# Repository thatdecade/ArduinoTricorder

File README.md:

# ArduinoTricorder
Interactive Tricorder Prop with real environmental sensors

Based on the original work by lambtor: https://github.com/lambtor/ArduinoTricorder

# Features

* Animated Lights and Sounds, Interactive Menus
* Thermal Camera (MLX90640)
* Climate Sensors: Humidity (SHT31), Temperature and barometric pressure (BMP280)
* Color Sensor and Distance Measurement (APDS9960)
* Microphone (PDM) FFT spectrum
* Auto Sleep when Door is Closed, uses Magnetometer (LIS3MDL)

# Usage

On Power up, the main screen is displayed and the sound effects start.  

* To navigate the info pages, press left or right.  Pressing center goes home.
* To toggle sound effects, hold the left button.
* Close the lid or wait 10 mins to put to sleep, low power mode.  Open the lid or press a button to wake up.

Thermal Camera: To access the video, press the button marked User SW on the Feather board.  If you did not install the thermal camera, the tricorder will display an error message.
Press the center button to return home.

# Part List

TBD

# 3D Printing

The case assembly notes are on printables: https://www.printables.com/model/225964-printability-remix-of-arduino-tricorder

# Wiring Diagram

Battery, Charger Jack, and Power Switch not shown.  See Adafruit Feather nRF52840 Sense docs.

I used a 2500mAh battery, but smaller would work fine too.  1000mAh - 2500mAh is recommended.

If you want to change any wires, use the pinmap.h file.  

# Software Setup

Follow the adafruit guide for setting up the Feather nRF52840 board package in Arduino. Then begin installing the libraries.
https://learn.adafruit.com/adafruit-feather-sense/arduino-support-setup

1. Copy the MLX90640_API folder from this repo's libraries folder to your arduino's libraries folder.  If you are unsure where this is, open Preferences from the Arduino File menu and look for the sktechbook location. Mine is My Documents\Arduino\libraries.
1. Install the following lilbraries.  Start with the latest versions.
> * Adafruit NeoPixel version 1.10.6
> * Adafruit TinyUSB Library version 1.7.0
> * Adafruit GFX Library version 1.11.3
> * Adafruit BusIO version 1.14.1
> * Adafruit ST7735 and ST7789 Library 
> * Adafruit APDS9960 Library version 1.2.2
> * Adafruit BMP280 Library version 2.6.6
> * Adafruit Unified Sensor version 1.1.6
> * Adafruit SHT31 Library version 2.2.0
> * nRF52840 PDM - Adafruit Fork version 1.0
> * Adafruit Zero FFT Library version 1.0.4
> * Adafruit LIS3MDL version 1.2.1
> * DFRobotDFPlayerMini version 1.0.5
3. Hit the Compile to test everything is as it should be.  If you get any errors, try switching to the version listed above.
4. Plug in the arduino to USB, and select Adafruit Feather nRF52840 Sense as the board, then select the port.
5. Hit Upload.

If all went well, you should see the display come alive.

# Bugs

* I used D13 for the BIO button input and needed to remove the Arduino's D13 onboard LED.  

On the Adafruit Feather nRF52840 Sense board, D13 is wired to an onboard LED (similar to other arduino boards).  D13 worked at first using INPUT_PULLUP, but eventually stopped working.  I measured the voltage on this pin at 1.9V when the button was unpressed, and 0.2V for pressed.  The nRF52840 requires at least 0.7xVcc to detect a digital high.  1.9V < 2.3V, so the chip thought the button was stuck pressed.  The LED + Resistor and INPUT_PULLUP were creating a voltage clamp at the diode's Forward Voltage.

My fix was unsoldering the D13 LED.  A better fix would be moving the BIO button input wire and reserving D13 as output only.

* Communication with the DFPlayer is inconsistant.

Likely due to me using a clone of the DFPlayer.  Work around is for the arduino to query the status from the DFPlayer every 500ms, then if the player is not playing when it should (or vice versa) we send the play/stop command again.  So if there is a glitch in the audio start / loop / stop, it is fixed quickly.

* Speaker Volume and Screen Flicker, reduce volume and use a larger battery

When the DFPlayer is set to max volume and the tricorder is powered by USB, I noticed the screen flickering from the speaker amp.  Switching to battery, the screen appears ok.

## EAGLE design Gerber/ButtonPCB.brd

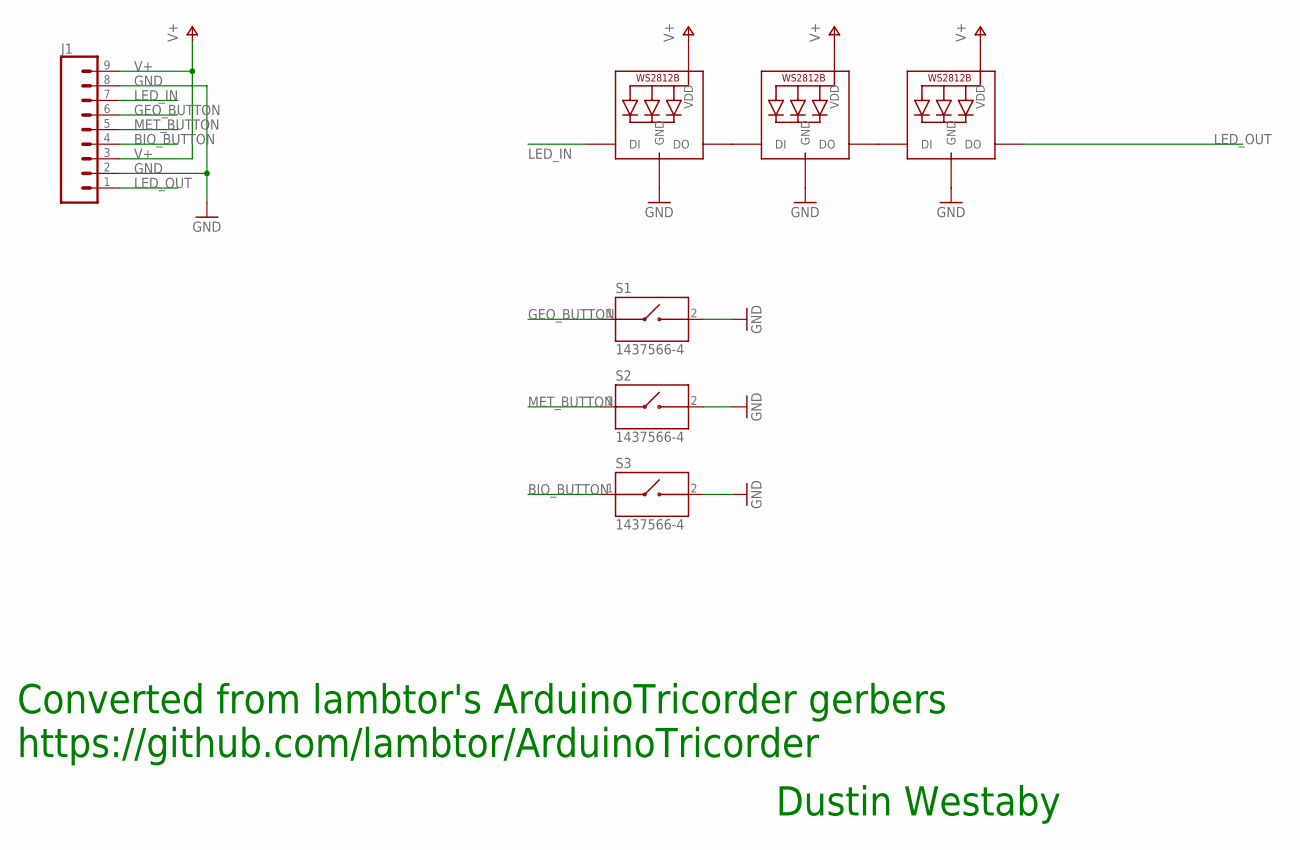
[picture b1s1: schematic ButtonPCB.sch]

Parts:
J1: CONN_09; 1X09
LED1, LED2, LED3: WS2812B_4020
S1, S2, S3: 1437566-4; SW_1437566-4

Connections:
BIO_BUTTON: J1.4, S3.1
GEO_BUTTON: J1.6, S1.1
GND: J1.2, J1.8, LED1.4 (GND), LED2.4 (GND), LED3.4 (GND), S1.2, S2.2, S3.2
LED_IN: J1.7, LED2.1 (DI)
LED_OUT: J1.1, LED3.3 (DO)
MET_BUTTON: J1.5, S2.1
unnamed: LED1.1 (DI), LED2.3 (DO)
unnamed: LED1.3 (DO), LED3.1 (DI)
V+: J1.3, J1.9, LED1.2 (VDD), LED2.2 (VDD), LED3.2 (VDD)

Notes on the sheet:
Converted from lambtor's ArduinoTricorder gerbers
https://github.com/lambtor/ArduinoTricorder
Dustin Westaby

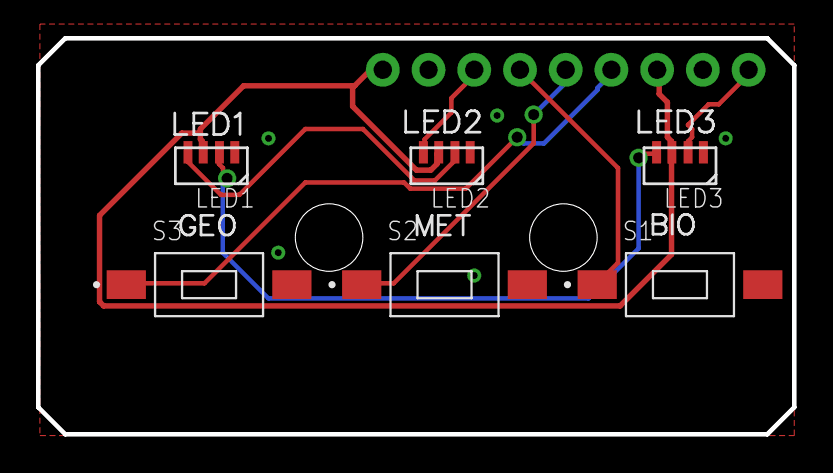
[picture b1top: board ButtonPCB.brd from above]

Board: 2 copper layers, 42.0 x 22.0 mm, 7 parts (1 on the bottom side), 9 nets.

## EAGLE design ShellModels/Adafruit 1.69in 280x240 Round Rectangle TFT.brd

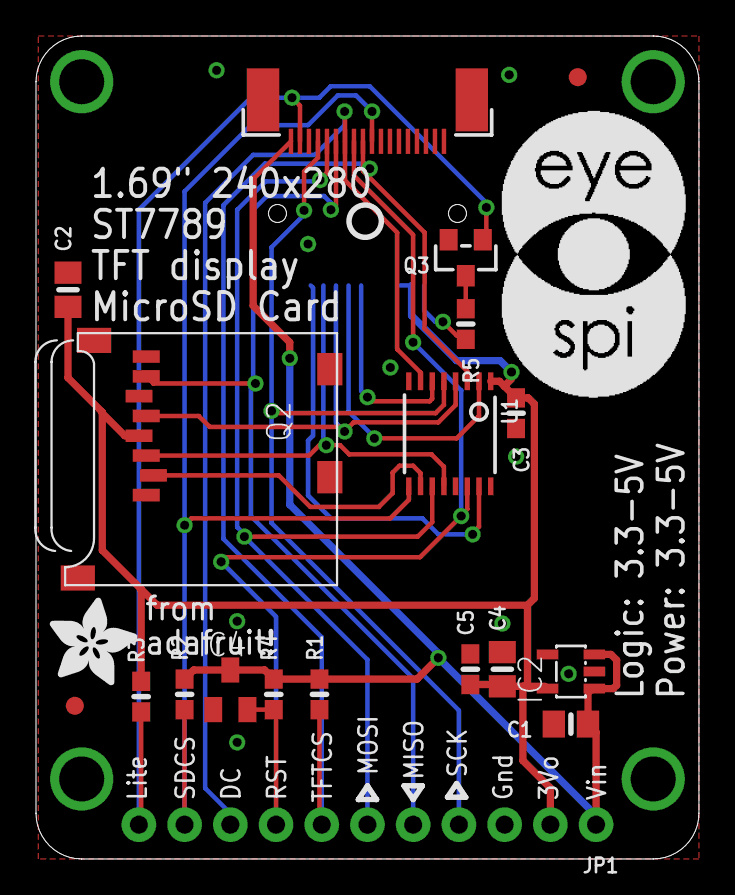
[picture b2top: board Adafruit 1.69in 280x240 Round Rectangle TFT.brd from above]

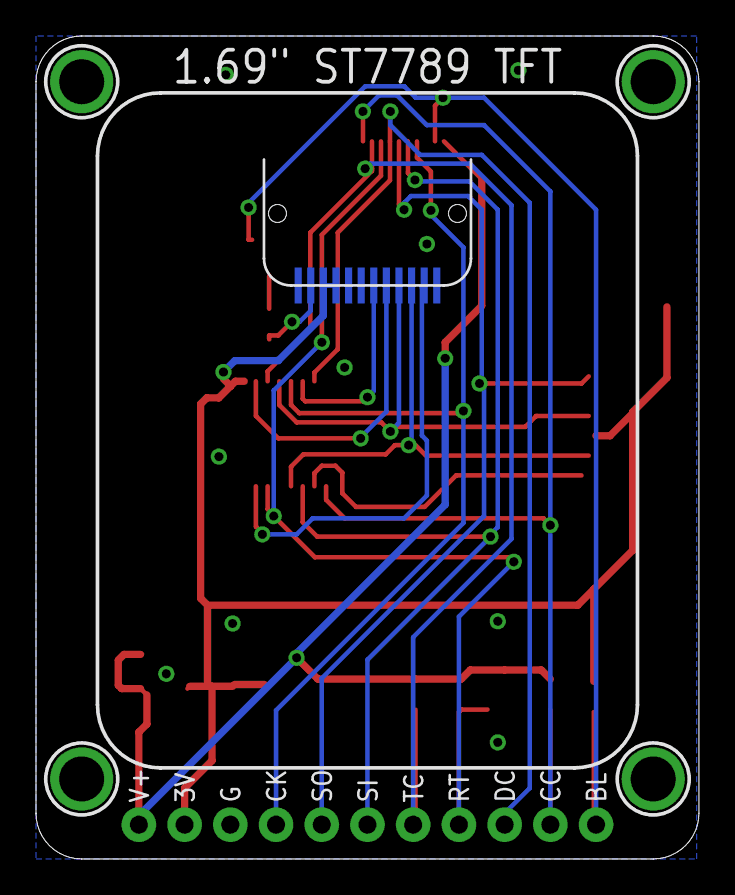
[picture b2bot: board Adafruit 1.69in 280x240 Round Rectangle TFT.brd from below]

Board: 2 copper layers, 36.8 x 45.7 mm, 27 parts (5 on the bottom side), 19 nets.

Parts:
C1, C2, C4: 10uF; 0805-NO
C3, C5: 0.1uF; 0603-NO
DISP1: DISP_LCD_GENERIC_SPI_1.69_WRAPUNDER; TFT_1.69IN_240X280_12P
IC2: AP2112; SOT23-5L
IC4: APX803-SAG; SOT23
JP1: 1X11_ROUND_76
Q2: MICROSD
Q3: BSS138; SOT23-WIDE
R1, R2, R3, R4: 10K; 0603-NO
R5: 10; 0603-NO
U1: 74HC4050PWR; TSSOP16
U$1: ADAFRUIT_5MM
U$2: PCBFEAT-REV-040
U$4, U$5: FIDUCIAL_1MM
U$7, U$8, U$9, U$10: MOUNTINGHOLE2.5; MOUNTINGHOLE_2.5_PLATED
U$19: EYESPI_LOGO
X1: EYE_SPI_DISPLAY_FLIP; EYE_SPI_DISPLAY_BOTCONTACT

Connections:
+3V3: C2.1, C3.1, C4.1, C5.1, DISP1.3, DISP1.4, IC2.5, JP1.2, Q2.4, R3.2, U1.1
CARDCS: JP1.10, R2.1, U1.9, X1.10
CARDCS_3V: Q2.2, U1.10
GND: C1.2, C2.2, C3.2, C4.2, C5.2, DISP1.1, DISP1.5, DISP1.6, DISP1.12, IC2.2, IC4.1, JP1.3, Q2.6, Q2.MT1, Q2.MT2, Q3.2, U1.8, X1.3, X1.SUPPORT1, X1.SUPPORT2
LEDK: DISP1.2, R5.2
LITE: JP1.11, Q3.1, R3.1, X1.2
MISO: JP1.5, Q2.7, X1.6
MOSI: JP1.6, U1.11, X1.5
MOSI_3V: DISP1.10, Q2.3, U1.12
unnamed: Q3.3, R5.1
SCK: JP1.4, U1.5, X1.4
SCK_3V: DISP1.9, Q2.5, U1.4
TFTCS: JP1.7, R1.1, U1.3, X1.9
TFTCS_3V: DISP1.8, U1.2
TFTDC: JP1.9, U1.7, X1.7
TFTDC_3V: DISP1.7, U1.6
TFTRST: IC4.2, JP1.8, R4.1, U1.14, X1.8
TFTRST_3V: DISP1.11, U1.15
VIN: C1.1, IC2.1, IC2.3, IC4.3, JP1.1, R1.2, R2.2, R4.2, X1.1

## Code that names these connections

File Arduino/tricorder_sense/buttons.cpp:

/*
 * buttons.c
 *
 *  Created on: Jul 15, 2020
 *      Author: Dustin Westaby
 */

#include "buttons.h"
#include "pinmap.h" // go here to set your own pin definitions

byte pinMap_buttons[NUMBER_OF_BUTTONS] =
{
  GEO_BUTTON_1_PIN,  // GEO_BUTTON
  MET_BUTTON_2_PIN,  // MET_BUTTON
  BIO_BUTTON_3_PIN,  // BIO_BUTTON
  CAM_BUTTON_BOARD,  // CAM_BUTTON
};

byte button_state[NUMBER_OF_BUTTONS] = 
{
  IS_NOT_PRESSED,  // GEO_BUTTON
  IS_NOT_PRESSED,  // MET_BUTTON
  IS_NOT_PRESSED,  // BIO_BUTTON
  IS_NOT_PRESSED,  // CAM_BUTTON
};

byte get_button_state(byte button)
{
  return button_state[button];
}

void poll_input_switches()
{
  static bool last_button_read[]    = {false, false, false, false};
  static bool current_button_read[] = {false, false, false, false};

  for(uint8_t i = 0; i < NUMBER_OF_BUTTONS; i++)
  {
    /* read digital active low button signal */
    current_button_read[i] = !digitalRead(pinMap_buttons[i]);

    if (!last_button_read[i] && current_button_read[i])
    {
      //button was just pressed
      button_state[i] = IS_PRESSED;
    }
    else if  (last_button_read[i] && current_button_read[i])
    {
      //button is being held
      button_state[i] = IS_HELD;
    }
    else if (last_button_read[i] && !current_button_read[i])
    {
      //button was just released
      button_state[i] = WAS_RELEASED;
    }
    else
    {
      button_state[i] = IS_NOT_PRESSED;
    }

    last_button_read[i] = current_button_read[i];
  }
}

void enable_input_switches()
{
  for(uint8_t i = 0; i < NUMBER_OF_BUTTONS; i++)
  {
		pinMode(pinMap_buttons[i], INPUT_PULLUP);
	}
}

void disable_input_switches()
{
  for(uint8_t i = 0; i < NUMBER_OF_BUTTONS; i++)
  {
		pinMode(pinMap_buttons[i], OUTPUT);
		digitalWrite(pinMap_buttons[i], HIGH);
	}
}

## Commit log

2022-05-23 Create LICENSE
2022-05-23 Converted to eagleCAD
2022-05-23 Compiled binary
2022-05-25 Basic body outline. Work in progress
2022-05-25 Swapped to smd buttons that I like.
2022-05-26 Some progress on the control panel
2022-05-26 circuit board models
2022-05-26 Added popouts to hold the panels in place before gluing
2022-05-26 Added screw hole mounts to button pcb
2022-05-27 lcd model
2022-05-27 Added lcd bezel
2022-05-31 Prep for project bring up
2022-05-31 Moved ino to subfolder
2022-05-31 Rewrote with new menu system to support next round of updates
2022-05-31 Minor cleanup
2022-05-31 Cleanup of globals
2022-05-31 Restored magnet sleep mode, moved neopixel animation controls to own function.
2022-05-31 Bug fix
2022-05-31 added sleep timer, narrowed ifdefs around magnet code, moved audio updates to own function
2022-05-31 Menu navigation is based on current screen
2022-05-31 Wiring Notes
2022-06-01 Neopixel code cleanup
2022-06-01 Prep for tft work
2022-06-01 minor updates, notes
2022-06-08 Insert-able hinge, for prettier print
2023-01-02 Debugged buttons, menus, and most lights.
2023-01-02 Sleep debugged, faster reaction to door closed.
2023-01-03 Debugged rgb sensor
2023-01-03 Added lcd backlight to the sleep
2023-01-04 Merged the various LED strip functions, fixed EMRG
2023-01-04 Fixed detection of camera connected / disconnected
2023-01-04 Updated pinouts to prep for dfplayer
2023-01-04 Added serial DFPlayer
2023-01-05 Debugged dfplayer init
2023-01-05 Moved audio player to it's own module and schedule
2023-01-05 Hold left button to toggle audio on/off
2023-01-06 Bug fixes
2023-01-06 Moved pin assignments to pinmap.h

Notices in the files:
parts and their libraries:
microbuilder: This work is placed in the public domain, and may be freely used for commercial and non-commercial work with the following conditions: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
SparkFun-Connectors: Licensing: Creative Commons ShareAlike 4.0 International - https://creativecommons.org/licenses/by-sa/4.0
